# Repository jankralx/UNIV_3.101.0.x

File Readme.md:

UNIV 3.101.0.x
============

RS232C INTERFACE - PC interface and interface to other devices with serial port

Device webpage: http://hapcan.com/devices/universal/univ_3/univ_3-101-0-x/

Hardware created in Eagle PCB Software http://www.cadsoftusa.com/

Firmware created in Microchip MPLAB http://www.microchip.com/mplabide/ in assembly language

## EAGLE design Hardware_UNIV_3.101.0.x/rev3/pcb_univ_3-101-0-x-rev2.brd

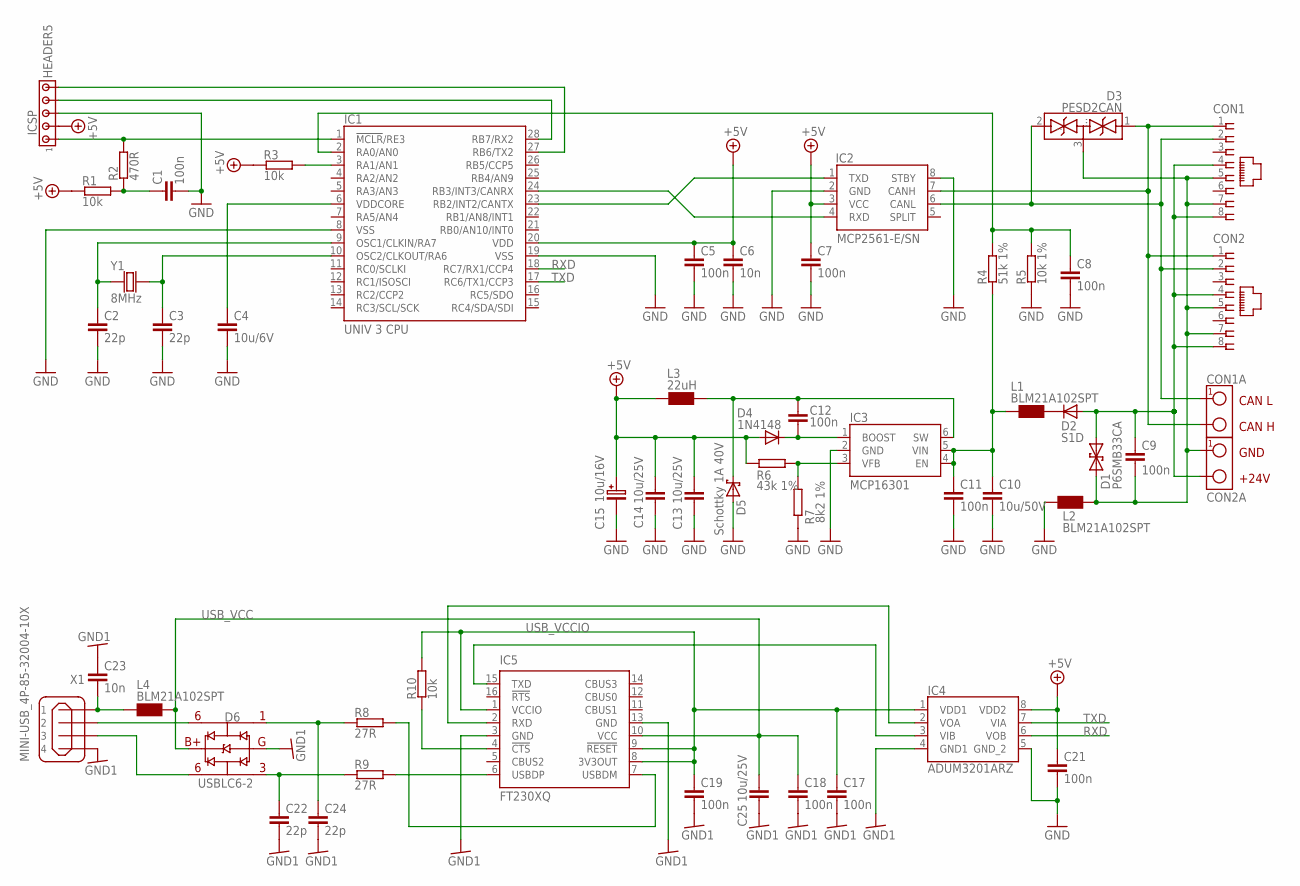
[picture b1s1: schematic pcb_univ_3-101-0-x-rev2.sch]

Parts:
C1, C5, C7, C8, C9, C11, C12, C17, C18, C19, C21: 100n; 0805
C2, C3, C22, C24: 22p; 0805
C4: 10u/6V; 0805
C6, C23: 10n; 0805
C10: 10u/50V; 1210
C13, C14, C25: 10u/25V; 1206
C15: 10u/16V; SMC_B
CON1, CON2: RJ45-SOCKET; RJ45-PCB-SOCKET
CON1A, CON2A: TERMINAL-2; ARK2-5X10,5MM
D1: P6SMB33CA; DO-214_TRANSIL2
D2: S1D; DO-214
D3: PESD2CAN; SOT-23
D4: 1N4148; 0805
D5: Schottky 1A 40V; DO-214
D6: USBLC6-2; SOT23-6L; MFR_PART_NO USBLC6-2SC6
IC1: UNIV 3 CPU; UNIV3CPU
IC2: MCP2561-E/SN; SO-08
IC3: MCP16301; SOT-23-6
IC4: ADUM3201ARZ; SOIC127P600X175-8N
IC5: FT230XQ; QFN16
ICSP: HEADER5; SIP-5
L1, L2, L4: BLM21A102SPT; 0805
L3: 22uH; CHOKE-DER0705
R1, R3, R10: 10k; 0805
R2: 470R; 0805
R4: 51k 1%; 0805
R5: 10k 1%; 0805
R6: 43k 1%; 0805
R7: 8k2 1%; 0805
R8, R9: 27R; 0805
X1: MINI-USB_4P-85-32004-10X; 85-32004-10X
Y1: 8MHz; CRYSTAL-HC49V

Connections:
+5V: C5.1, C6.1, C7.1, C13.1, C14.1, C15.+ (1), C21.1, D4.2 (A), IC1.20 (VDD), IC2.3 (VCC), IC4.8 (VDD2), ICSP.2, L3.1, R1.1, R3.1, R6.1
GND: C1.2, C2.2, C3.2, C4.2, C5.2, C6.2, C7.2, C8.2, C10.2, C11.2, C13.2, C14.2, C15.- (2), C21.2, D5.A, IC1.8 (VSS), IC1.19 (VSS), IC2.2 (GND), IC2.8 (STBY), IC3.2 (GND), IC4.5 (GND_2), ICSP.3, L2.1, R5.1, R7.1
GNDIO: C17.2, C18.2, C19.2, C22.2, C23.1, C24.2, C25.2, D6.2 (G), IC4.4 (GND1), IC5.3 (GND), IC5.13 (GND), X1.4
ICSP: IC1.1 (!MCLR!/RE3), ICSP.1, R2.2
unnamed: D6.6, X1.2
unnamed: IC1.24 (RB3/INT3/CANRX), IC2.4 (RXD)
unnamed: IC1.23 (RB2/INT2/CANTX), IC2.1 (TXD)
unnamed: D6.4, X1.3
unnamed: C12.1, D5.C, IC3.6 (SW), L3.2
unnamed: IC3.3 (VFB), R6.2, R7.2
unnamed: C1.1, R1.2, R2.1
unnamed: C8.1, IC1.2 (RA0/AN0), R4.2, R5.2
unnamed: CON1.1, CON1A.2, CON2.1, D3.1 (.), IC2.7 (CANH)
unnamed: IC1.28 (RB7/RX2), ICSP.4
unnamed: C2.1, IC1.9 (OSC1/CLKIN/RA7), Y1.1
unnamed: IC1.3 (RA1/AN1), R3.2
unnamed: CON1.2, CON1A.1, CON2.2, D3.2 (..), IC2.6 (CANL)
unnamed: IC1.27 (RB6/TX2), ICSP.5
unnamed: C3.1, IC1.10 (OSC2/CLKOUT/RA6), Y1.2
unnamed: C10.1, C11.1, IC3.4 (EN), IC3.5 (VIN), L1.1, R4.1
unnamed: C23.2, L4.2, X1.1
unnamed: C9.2, CON1.5, CON1.7, CON2.5, CON2.7, CON2A.1, D1.C (2), D3.3 (...), L2.2
unnamed: IC4.2 (VOA), IC5.2 (RXD)
unnamed: C24.1, D6.1, R8.1
unnamed: C22.1, D6.3, R9.1
unnamed: IC5.6 (USBDP), R9.2
unnamed: IC5.7 (USBDM), R8.2
unnamed: IC4.3 (VIB), IC5.15 (TXD)
unnamed: IC5.4 (!CTS), R10.1
unnamed: C12.2, D4.1 (C), IC3.1 (BOOST)
unnamed: C4.1, IC1.6 (VDDCORE)
unnamed: C9.1, CON1.4, CON1.8, CON2.4, CON2.8, CON2A.2, D1.A (1), D2.A
unnamed: D2.C, L1.2
RXD: IC1.18 (RC7/RX1/CCP4), IC4.6 (VOB)
TXD: IC1.17 (RC6/TX1/CCP3), IC4.7 (VIA)
USB_VCC: C18.1, C25.1, D6.5 (B+), IC5.10 (VCC), L4.1
USB_VCCIO: C17.1, C19.1, IC4.1 (VDD1), IC5.1 (VCCIO), IC5.8 (3V3OUT), IC5.9 (!RESET), R10.2

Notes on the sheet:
CAN L
CAN H
GND
+24V

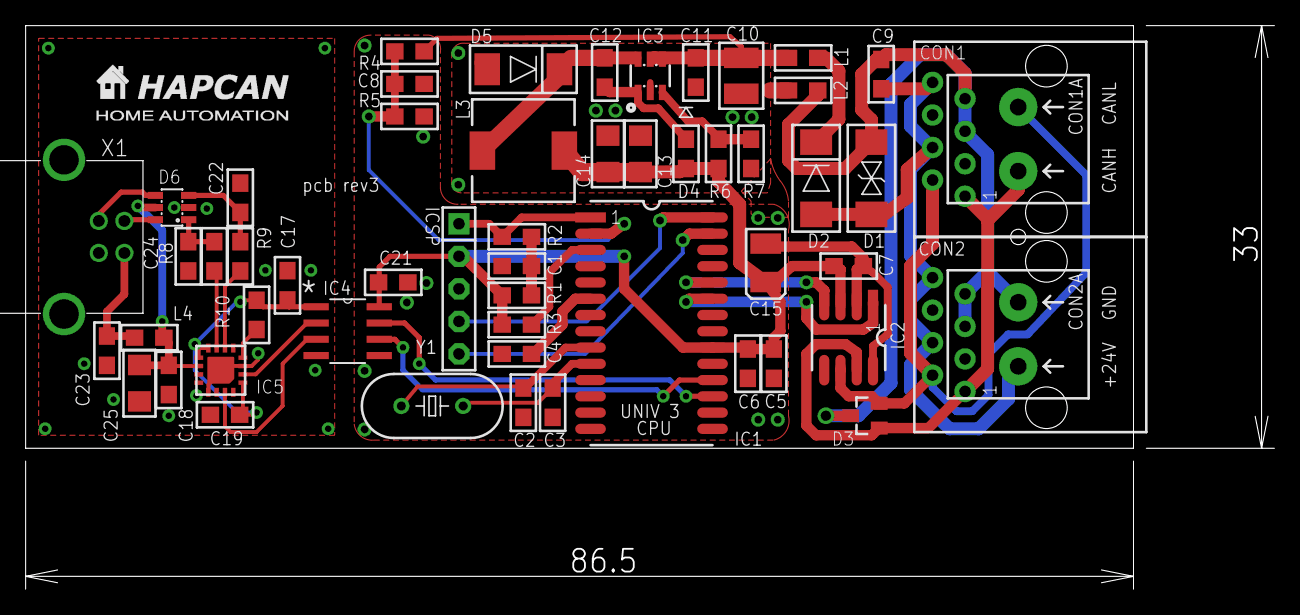
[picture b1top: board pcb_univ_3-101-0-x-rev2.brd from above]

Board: 2 copper layers, 86.5 x 33.0 mm, 55 parts (0 on the bottom side), 37 nets.

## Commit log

2013-09-26 hardware revision 0
2013-09-26 firmware revision 0
2014-08-10 firmware UNIV 3.101.0.1 revision 0
2016-05-28 hardware UNIV 3.101.0.x revision 0
2016-05-28 hardware UNIV 3.101.0.x revision 1
2017-12-28 firmware UNIV 3.101.0.1 revision 1
2021-07-23 hardware UNIV 3.101.0.x revision 2
2024-07-04 (hardware) rev3 with RS233 via FTDI USB and ADUM isolators
